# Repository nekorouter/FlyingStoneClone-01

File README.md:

# FlyingStoneClone-01
Gnuk-compatible GnuPG USB Token

## Reasons for starting this project

Because I lost my old GPG key's password and need a better way to carry GPG key with me.

Hardware key + paperkey seems like a better solution, and luckily I met with Niibe Yutaka, who made a open-source GPG USB key project called Gnuk Token. 

## Design Considerations

- STM32F103CBT6 is more hand-soldering friendly
- ST-Link v2 can be used as testing platform
- If the hardware looks more like a ST-Link than a some mystical USB stick, it may have some "camouflage" for that
- Maybe I can use those left board as a ST-Link...
- Possibility of adding a ACK button

## Difference from FlyingStone-01/FlyingStone-01-G/FlyingStone-01-ShenZhen

FST-01:
- STM32F103TB, 12MHz XTAL
- PA2,PA3 exposed

FST-01G:
- Using the same MCU/XTAL as FST-01

FST-01SZ:
- GD32F103TB, 12MHz XTAL
- PA3 exposed by using a hall effect sensor (DRV5032FA)

FSC-01:
- STM32F103CB, 8MHz XTAL
- PA5,PB0,PB13,PB14,PA2,PA3 exposed, in which PA5 is designed to be used as ACK button

## What need to be done next

- test if Gnuk is function correctly
- test if NeuG is working
- test ESD safety
- test if this board can be used as ST-Link v2

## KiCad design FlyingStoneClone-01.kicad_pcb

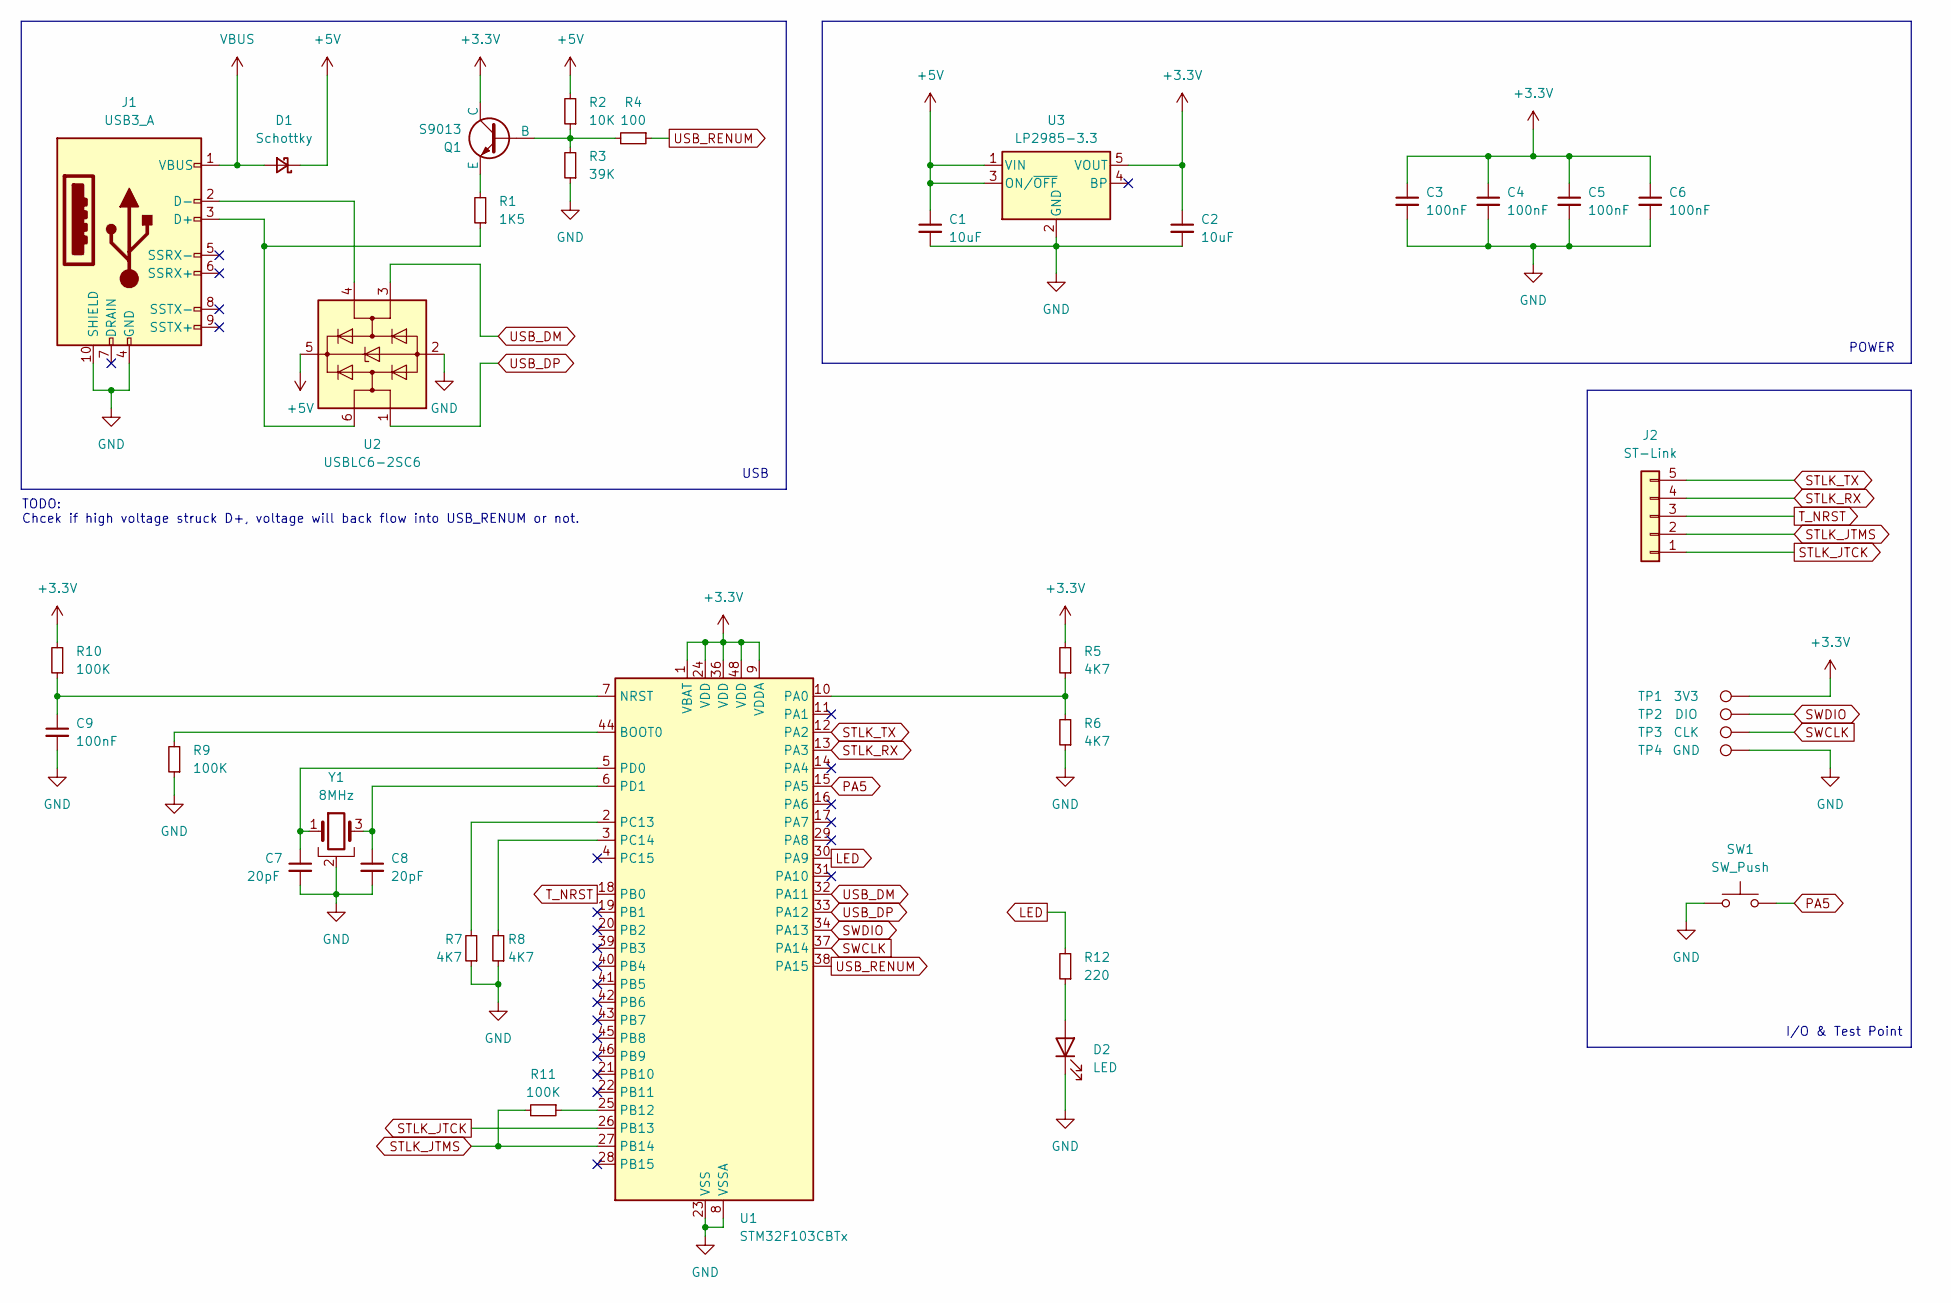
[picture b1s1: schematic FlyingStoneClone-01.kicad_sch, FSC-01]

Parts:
C1, C2: 10uF; C_0402_1005Metric_Pad0.74x0.62mm_HandSolder
C3, C4, C5, C6, C9: 100nF; C_0402_1005Metric_Pad0.74x0.62mm_HandSolder
C7, C8: 20pF; C_0402_1005Metric_Pad0.74x0.62mm_HandSolder
D1: Schottky; D_SOD-523
D2: LED; LED_0402_1005Metric_Pad0.77x0.64mm_HandSolder
J1: USB3_A; USB3_A_Plug_Wuerth_692112030100_Horizontal
J2: ST-Link; PinHeader_1x05_P2.54mm_Vertical
Q1: S9013; SOT-23
R1: 1K5; R_0402_1005Metric_Pad0.72x0.64mm_HandSolder
R2: 10K; R_0402_1005Metric_Pad0.72x0.64mm_HandSolder
R3: 39K; R_0402_1005Metric_Pad0.72x0.64mm_HandSolder
R4: 100; R_0402_1005Metric_Pad0.72x0.64mm_HandSolder
R5, R6, R7, R8: 4K7; R_0402_1005Metric_Pad0.72x0.64mm_HandSolder
R9, R10, R11: 100K; R_0402_1005Metric_Pad0.72x0.64mm_HandSolder
R12: 220; R_0402_1005Metric_Pad0.72x0.64mm_HandSolder
SW1: SW_Push; TestPoint_2Pads_Pitch2.54mm_Drill0.8mm
TP1: 3V3; TestPoint_Pad_D1.0mm
TP2: DIO; TestPoint_Pad_D1.0mm
TP3: CLK; TestPoint_Pad_D1.0mm
TP4: GND; TestPoint_Pad_D1.0mm
U1: STM32F103CBTx; LQFP-48_7x7mm_P0.5mm
U2: USBLC6-2SC6; SOT-23-6
U3: LP2985-3.3; SOT-23-5
Y1: 8MHz; Crystal_SMD_3225-4Pin_3.2x2.5mm_HandSoldering

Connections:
+3.3V: C2.1, C3.1, C4.1, C5.1, C6.1, Q1.1 (C), R5.2, R10.2, TP1.1, U1.1 (VBAT), U1.9 (VDDA), U1.24 (VDD), U1.36 (VDD), U1.48 (VDD), U3.5 (VOUT)
+5V: C1.1, D1.1 (K), R2.2, U2.5 (VBUS), U3.1 (VIN), U3.3 (ON/~OFF)
GND: C1.2, C2.2, C3.2, C4.2, C5.2, C6.2, C7.2, C8.2, C9.2, D2.1 (K), J1.4 (GND), J1.10 (SHIELD), R3.1, R6.1, R7.1, R8.1, R9.1, SW1.1, TP4.1, U1.8 (VSSA), U1.23 (VSS), U1.35 (VSS), U1.47 (VSS), U2.2 (GND), U3.2 (GND), Y1.2
LED: R12.2, U1.30 (PA9)
unnamed: D2.2 (A), R12.1
unnamed: J1.3 (D+), R1.1, U2.6 (I/O1)
unnamed: J1.2 (D-), U2.4 (I/O2)
unnamed: Q1.2 (B), R2.1, R3.2, R4.2
unnamed: Q1.3 (E), R1.2
unnamed: R9.2, U1.44 (BOOT0)
unnamed: C9.1, R10.1, U1.7 (NRST)
unnamed: R5.1, R6.2, U1.10 (PA0)
unnamed: R11.1, U1.25 (PB12)
unnamed: R7.2, U1.2 (PC13)
unnamed: R8.2, U1.3 (PC14)
unnamed: C7.1, U1.5 (PD0), Y1.1
unnamed: C8.1, U1.6 (PD1), Y1.3
PA5: SW1.2, U1.15 (PA5)
STLK_JTCK: J2.1, U1.26 (PB13)
STLK_JTMS: J2.2, R11.2, U1.27 (PB14)
STLK_RX: J2.4, U1.13 (PA3)
STLK_TX: J2.5, U1.12 (PA2)
SWCLK: TP3.1, U1.37 (PA14)
SWDIO: TP2.1, U1.34 (PA13)
T_NRST: J2.3, U1.18 (PB0)
USB_DM: U1.32 (PA11), U2.3 (I/O2)
USB_DP: U1.33 (PA12), U2.1 (I/O1)
USB_RENUM: R4.1, U1.38 (PA15)
VBUS: D1.2 (A), J1.1 (VBUS)

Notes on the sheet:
I/O & Test Point
TODO: Chcek if high voltage struck D+, voltage will back flow into USB_RENUM or not.
POWER
USB

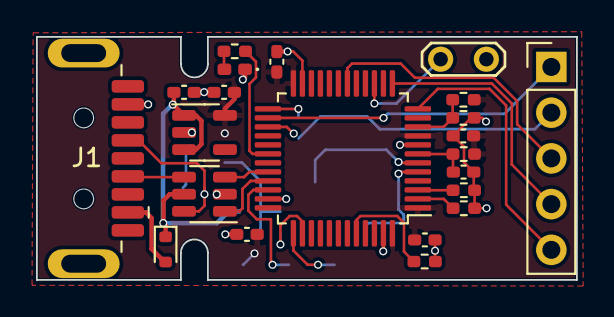
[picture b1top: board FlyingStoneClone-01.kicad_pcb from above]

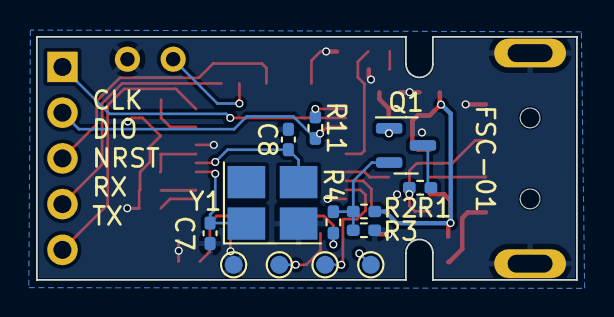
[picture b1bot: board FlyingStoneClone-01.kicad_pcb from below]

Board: 2 copper layers, 30.0 x 13.5 mm, 35 parts (13 on the bottom side), 29 nets.

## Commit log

2024-10-09 Upload design: First version
